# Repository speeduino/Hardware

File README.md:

<div align="center">

[]

##### A low cost, DIY friendly Engine Management System (ECU) based on the Arduino framework
</div>

## Speeduino
The Speeduino project is a flexible, fully featured Engine Management Systems (EMS aka ECU) based on the low cost and open source Arduino platform. It provides the hardware, firmware and software components that make up an engine management system, all provided under open licenses. With over 1000 installations, Speeduino has matured into a product that meets the needs of the hobbyist and enthusiast community without driving prices to the levels of traditional aftermarket ECUs.

## Overview
This repositiory contains the official Speeduino hardware designs. All new designs have been made in Kicad, with some early boards developed in Fritzing. 

## License
These designs are release under the [CERN Open Hardware License v2 Strong (CERN-OHL-S)](https://ohwr.org/cern_ohl_s_v2.txt). 
This license is similar to the GPL, however is designed specifically for hardware design files, including PCB layouts and schematics. As the 'strongly reciprocal' version of the CERN OHL is used, you may use, copy, modify and create variations of these designs freely, provided that any changes or variations are also released under this CERN-OHL-S. 

## Where to Buy
[Pre-made Speeduino units/boards are available from a number of official resellers](https://speeduino.com/home/where-to-buy)

These resellers all contribute a portion of sales back to the project to allow for continued development to take place and we encourage sales through them whenever possible. 
 
Of course, being open source, you are free to use the design files provided here to create your own hardware! 

## Support
In addition the manual referenced above, Speeduino has a large and very vibrant community of people to help out with your setup or any questions you might add. 

* [Speeduino Forum](https://speeduino.com/forum) 
* [Discord](hhttps://discord.com/invite/taXeNM6xNb)
* [Facebook](https://www.facebook.com/groups/191918764521976/)

## Contributors

This project exists thanks to all the people who contribute, both in terms of code and testing provided. If you'd like to get involved, please have a read through [Contributing](contributing.md) and then jump on Discord to discuss things further

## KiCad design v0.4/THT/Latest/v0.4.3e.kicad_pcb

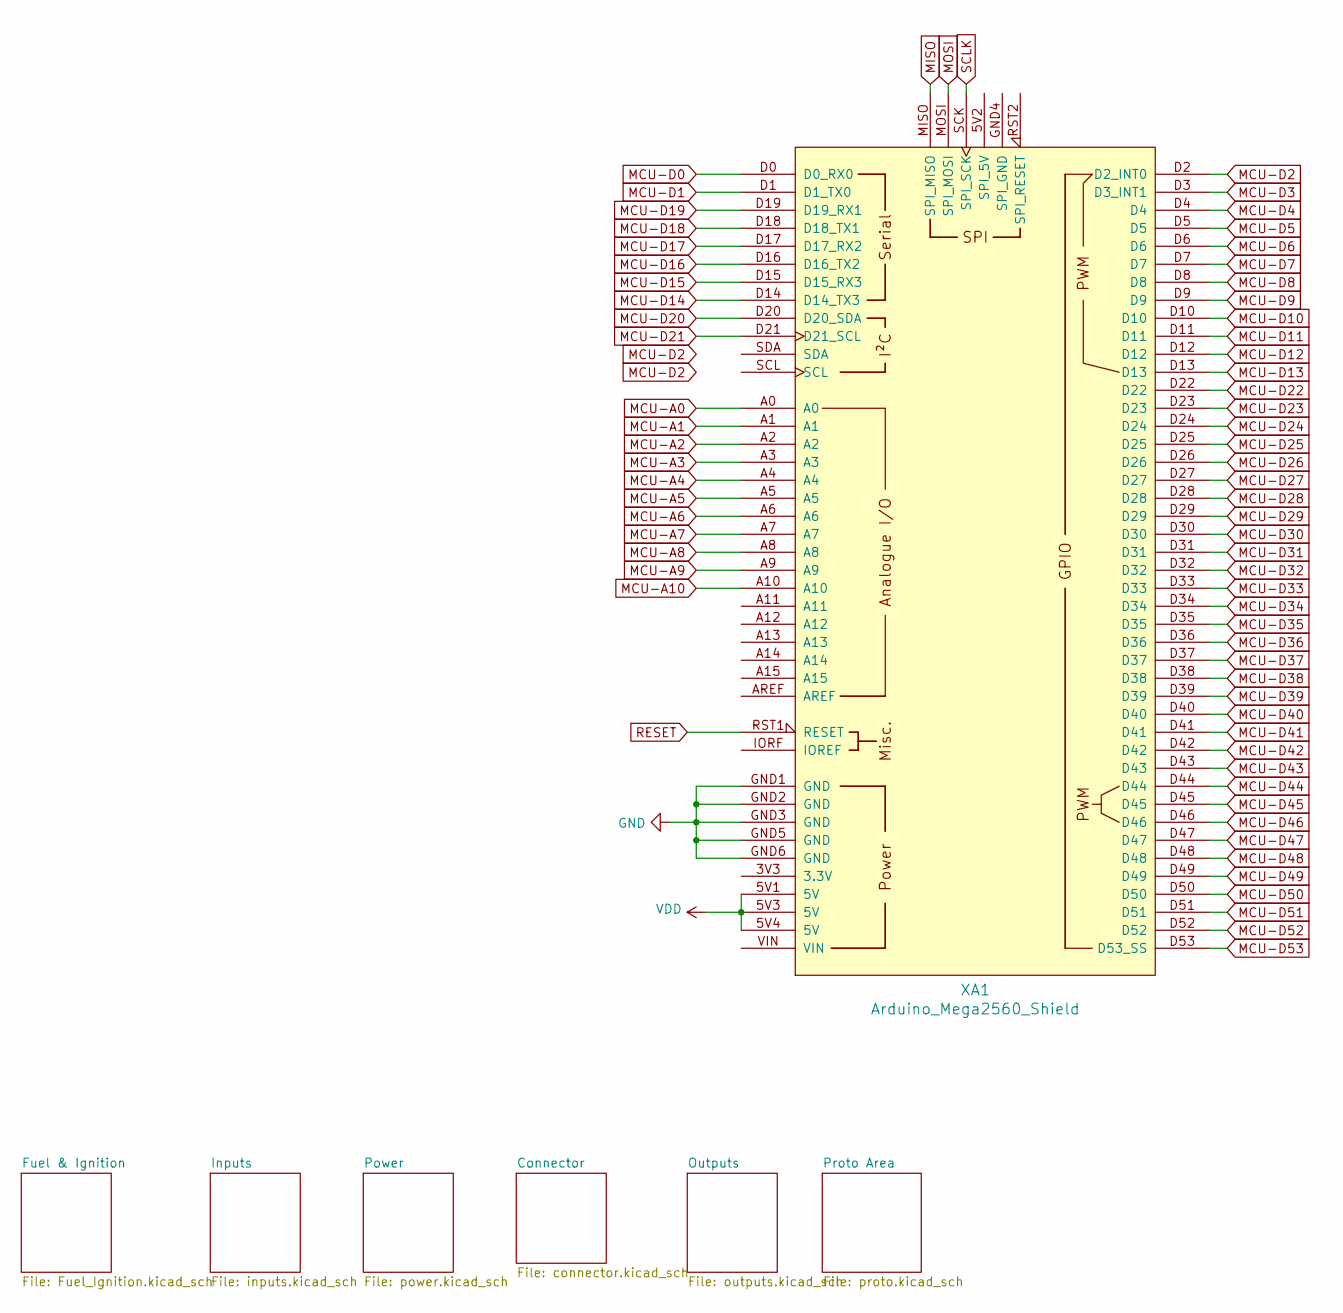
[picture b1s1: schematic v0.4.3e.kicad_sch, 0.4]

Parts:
XA1: Arduino_Mega2560_Shield; Arduino_Mega2560_Shield_IO_Only

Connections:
ADC-Clamp-2: XA1.A3; also elsewhere on the board
ADC-Clamp-3: XA1.A2; also elsewhere on the board
ADC-Clamp-5: XA1.A0; also elsewhere on the board
ADC-Clamp-6: XA1.A1; also elsewhere on the board
ADC-Clamp-7: XA1.D2 (D2_INT0); also elsewhere on the board
ADC-Clamp-8: XA1.D18 (D18_TX1); also elsewhere on the board
ADC-Clamp-9: XA1.D19 (D19_RX1); also elsewhere on the board
ADC-Clamp-10: XA1.D51; also elsewhere on the board
ADC-Clamp-11: XA1.A8; also elsewhere on the board
ADC-Clamp-12: XA1.A4; also elsewhere on the board
GND: XA1.GND1 (GND), XA1.GND2 (GND), XA1.GND3 (GND), XA1.GND5 (GND), XA1.GND6 (GND); also elsewhere on the board
MCU-A5: XA1.A5; also elsewhere on the board
MCU-A6: XA1.A6
MCU-A7: XA1.A7
MCU-A9: XA1.A9; also elsewhere on the board
MCU-A10: XA1.A10; also elsewhere on the board
MCU-D0: XA1.D0 (D0_RX0); also elsewhere on the board
MCU-D1: XA1.D1 (D1_TX0); also elsewhere on the board
MCU-D3: XA1.D3 (D3_INT1); also elsewhere on the board
MCU-D4: XA1.D4; also elsewhere on the board
MCU-D5: XA1.D5; also elsewhere on the board
MCU-D6: XA1.D6; also elsewhere on the board
MCU-D7: XA1.D7; also elsewhere on the board
MCU-D8: XA1.D8; also elsewhere on the board
MCU-D9: XA1.D9; also elsewhere on the board
MCU-D10: XA1.D10; also elsewhere on the board
MCU-D11: XA1.D11; also elsewhere on the board
MCU-D12: XA1.D12
MCU-D13: XA1.D13
MCU-D14: XA1.D14 (D14_TX3)
MCU-D15: XA1.D15 (D15_RX3)
MCU-D16: XA1.D16 (D16_TX2); also elsewhere on the board
MCU-D17: XA1.D17 (D17_RX2); also elsewhere on the board
MCU-D20: XA1.D20 (D20_SDA); also elsewhere on the board
MCU-D21: XA1.D21 (D21_SCL); also elsewhere on the board
MCU-D22: XA1.D22
MCU-D23: XA1.D23
MCU-D24: XA1.D24; also elsewhere on the board
MCU-D25: XA1.D25
MCU-D26: XA1.D26
MCU-D27: XA1.D27
MCU-D28: XA1.D28
MCU-D29: XA1.D29
MCU-D30: XA1.D30
MCU-D31: XA1.D31
MCU-D32: XA1.D32
MCU-D33: XA1.D33
MCU-D34: XA1.D34
MCU-D35: XA1.D35
MCU-D36: XA1.D36
MCU-D37: XA1.D37
MCU-D38: XA1.D38; also elsewhere on the board
MCU-D39: XA1.D39
MCU-D40: XA1.D40; also elsewhere on the board
MCU-D41: XA1.D41
MCU-D42: XA1.D42
MCU-D43: XA1.D43
MCU-D44: XA1.D44
MCU-D45: XA1.D45; also elsewhere on the board
MCU-D46: XA1.D46
MCU-D47: XA1.D47; also elsewhere on the board
MCU-D48: XA1.D48
MCU-D49: XA1.D49; also elsewhere on the board
MCU-D50: XA1.D50; also elsewhere on the board
MCU-D52: XA1.D52; also elsewhere on the board
MCU-D53: XA1.D53 (D53_SS)
RESET: XA1.RST1 (RESET); also elsewhere on the board
VDD: XA1.5V1 (5V), XA1.5V3 (5V), XA1.5V4 (5V); also elsewhere on the board

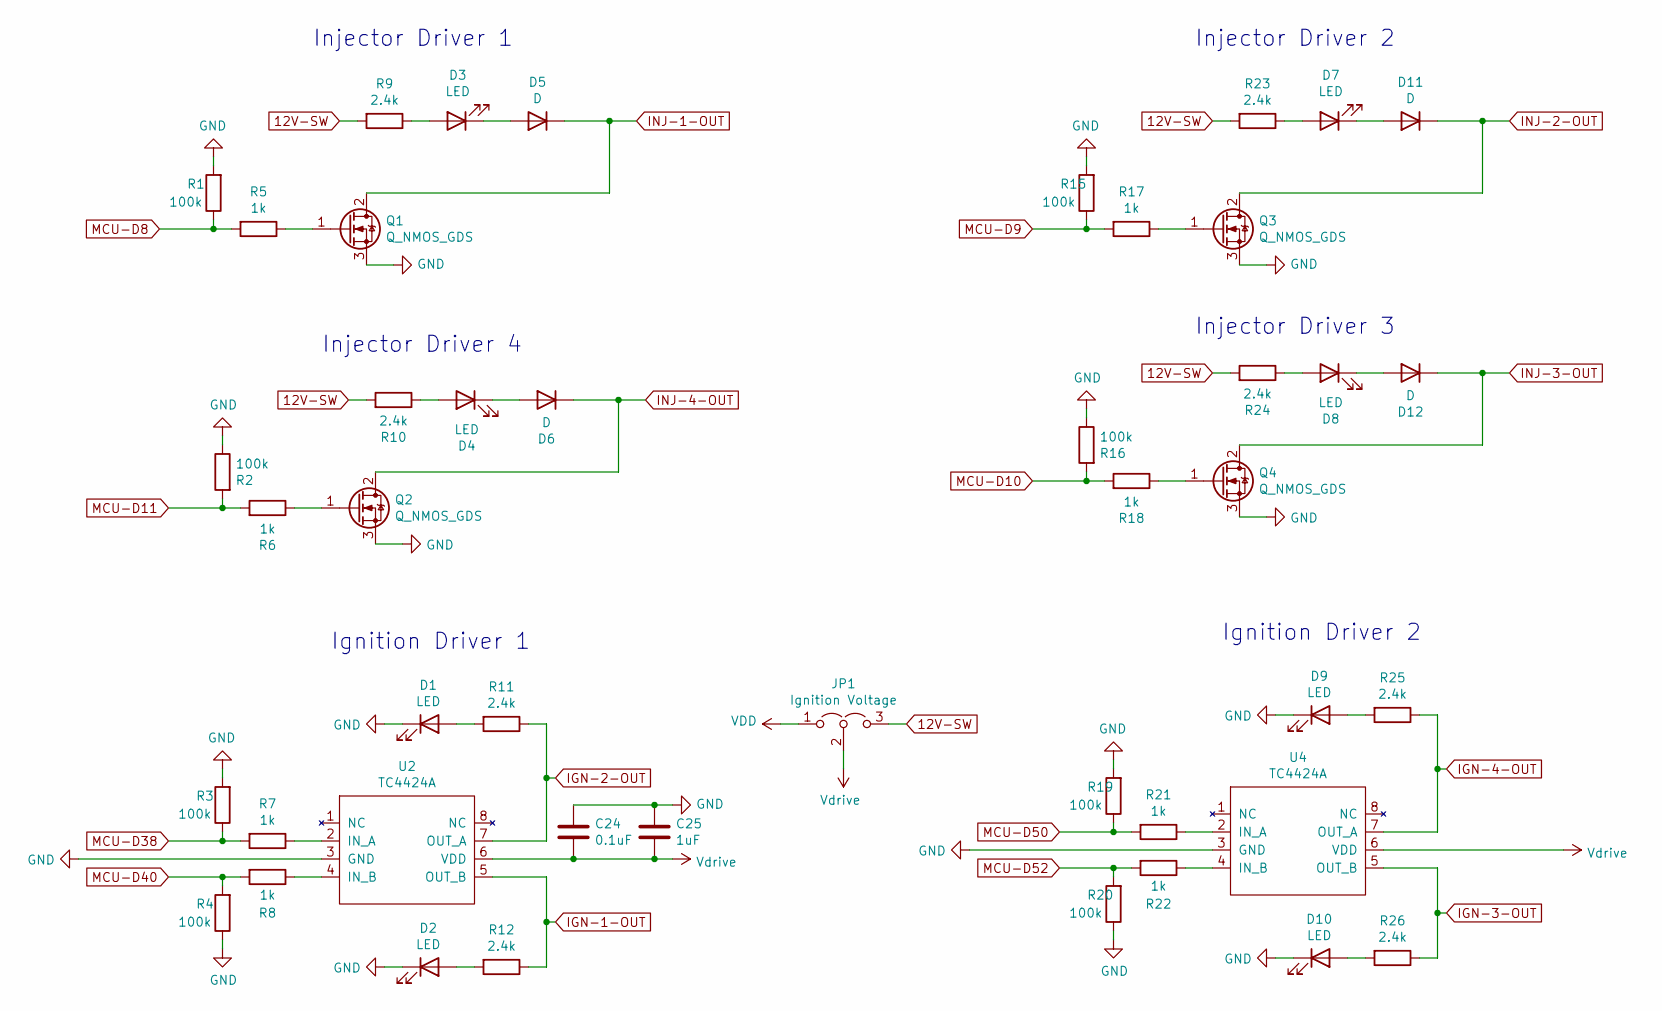
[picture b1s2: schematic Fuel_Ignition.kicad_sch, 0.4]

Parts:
C24: 0.1uF; C_Disc_D5.0mm_W2.5mm_P2.50mm; Manufacturer_Part_Number FA18X8R1E104KNU06; Digikey Part Number 445-180563-1-ND
C25: 1uF; C_Disc_D5.0mm_W2.5mm_P2.50mm; Manufacturer_Part_Number FA18X7R1E105KRU06; Digikey Part Number 445-180543-1-ND
D1, D2, D3, D4, D7, D8, D9, D10: LED; LED_D3.0mm; Manufacturer_Part_Number 151031SS04000; Digikey Part Number 732-5005-ND
D5, D6, D11, D12: D; D_DO-35_SOD27_P7.62mm_Horizontal; Manufacturer_Part_Number 1N914TAP; Digikey Part Number 1N914TAPGICT-ND
JP1: Ignition Voltage; PinHeader_1x03_P2.54mm_Vertical; Manufacturer_Part_Number M20-9990345; Digikey Part Number 952-2263-ND
Q1, Q2, Q3, Q4: Q_NMOS_GDS; TO-220-3_Horizontal_TabDown; Manufacturer_Part_Number STP62NS04Z; Digikey Part Number 497-5896-5-ND
R1, R2, R3, R4, R15, R16, R19, R20: 100k; R_Axial_DIN0204_L3.6mm_D1.6mm_P5.08mm_Horizontal; Manufacturer_Part_Number MBA02040C1003FCT00; Digikey Part Number BC3240CT-ND
R5, R6, R7, R8, R17, R18, R21, R22: 1k; R_Axial_DIN0204_L3.6mm_D1.6mm_P5.08mm_Horizontal; Manufacturer_Part_Number MBA02040C1001FRP00; Digikey Part Number BC1.00KXCT-ND
R9, R10, R11, R12, R23, R24, R25, R26: 2.4k; R_Axial_DIN0204_L3.6mm_D1.6mm_P5.08mm_Horizontal; Manufacturer_Part_Number MBA02040C2401FC100; Digikey Part Number BC3483CT-ND
U2, U4: TC4424A; DIP-8_W7.62mm_Socket; Manufacturer_Part_Number TC4424AVPA; Digikey Part Number TC4424AVPA-ND

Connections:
12V-SW: JP1.3 (B), R9.2, R10.2, R23.2, R24.2; also elsewhere on the board
GND: C24.1, C25.1, D1.1 (K), D2.1 (K), D9.1 (K), D10.1 (K), Q1.3 (S), Q2.3 (S), Q3.3 (S), Q4.3 (S), R1.2, R2.1, R3.2, R4.1, R15.2, R16.1, R19.2, R20.1, U2.3 (GND), U4.3 (GND); also elsewhere on the board
IGN-1-OUT: R12.1, U2.5 (OUT_B); also elsewhere on the board
IGN-2-OUT: R11.1, U2.7 (OUT_A); also elsewhere on the board
IGN-3-OUT: R26.1, U4.5 (OUT_B); also elsewhere on the board
IGN-4-OUT: R25.1, U4.7 (OUT_A); also elsewhere on the board
INJ-1-OUT: D5.1 (K), Q1.2 (D); also elsewhere on the board
INJ-2-OUT: D11.1 (K), Q3.2 (D); also elsewhere on the board
INJ-3-OUT: D12.1 (K), Q4.2 (D); also elsewhere on the board
INJ-4-OUT: D6.1 (K), Q2.2 (D); also elsewhere on the board
MCU-D8: R1.1, R5.2; also elsewhere on the board
MCU-D9: R15.1, R17.2; also elsewhere on the board
MCU-D10: R16.2, R18.2; also elsewhere on the board
MCU-D11: R2.2, R6.2; also elsewhere on the board
MCU-D38: R3.1, R7.2; also elsewhere on the board
MCU-D40: R4.2, R8.2; also elsewhere on the board
MCU-D50: R19.1, R21.2; also elsewhere on the board
MCU-D52: R20.2, R22.2; also elsewhere on the board
unnamed: D1.2 (A), R11.2
unnamed: D2.2 (A), R12.2
unnamed: D3.1 (K), D5.2 (A)
unnamed: D3.2 (A), R9.1
unnamed: D4.1 (K), D6.2 (A)
unnamed: D4.2 (A), R10.1
unnamed: D7.2 (A), R23.1
unnamed: D8.2 (A), R24.1
unnamed: D9.2 (A), R25.2
unnamed: D10.2 (A), R26.2
unnamed: D7.1 (K), D11.2 (A)
unnamed: D8.1 (K), D12.2 (A)
unnamed: Q1.1 (G), R5.1
unnamed: Q2.1 (G), R6.1
unnamed: Q3.1 (G), R17.1
unnamed: Q4.1 (G), R18.1
unnamed: R7.1, U2.2 (IN_A)
unnamed: R8.1, U2.4 (IN_B)
unnamed: R21.1, U4.2 (IN_A)
unnamed: R22.1, U4.4 (IN_B)
VDD: JP1.1 (A); also elsewhere on the board
Vdrive: C24.2, C25.2, JP1.2 (C), U2.6 (VDD), U4.6 (VDD)

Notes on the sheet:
Injector Driver 4
Ignition Driver 1
Injector Driver 3
Injector Driver 2
Injector Driver 1
Ignition Driver 2

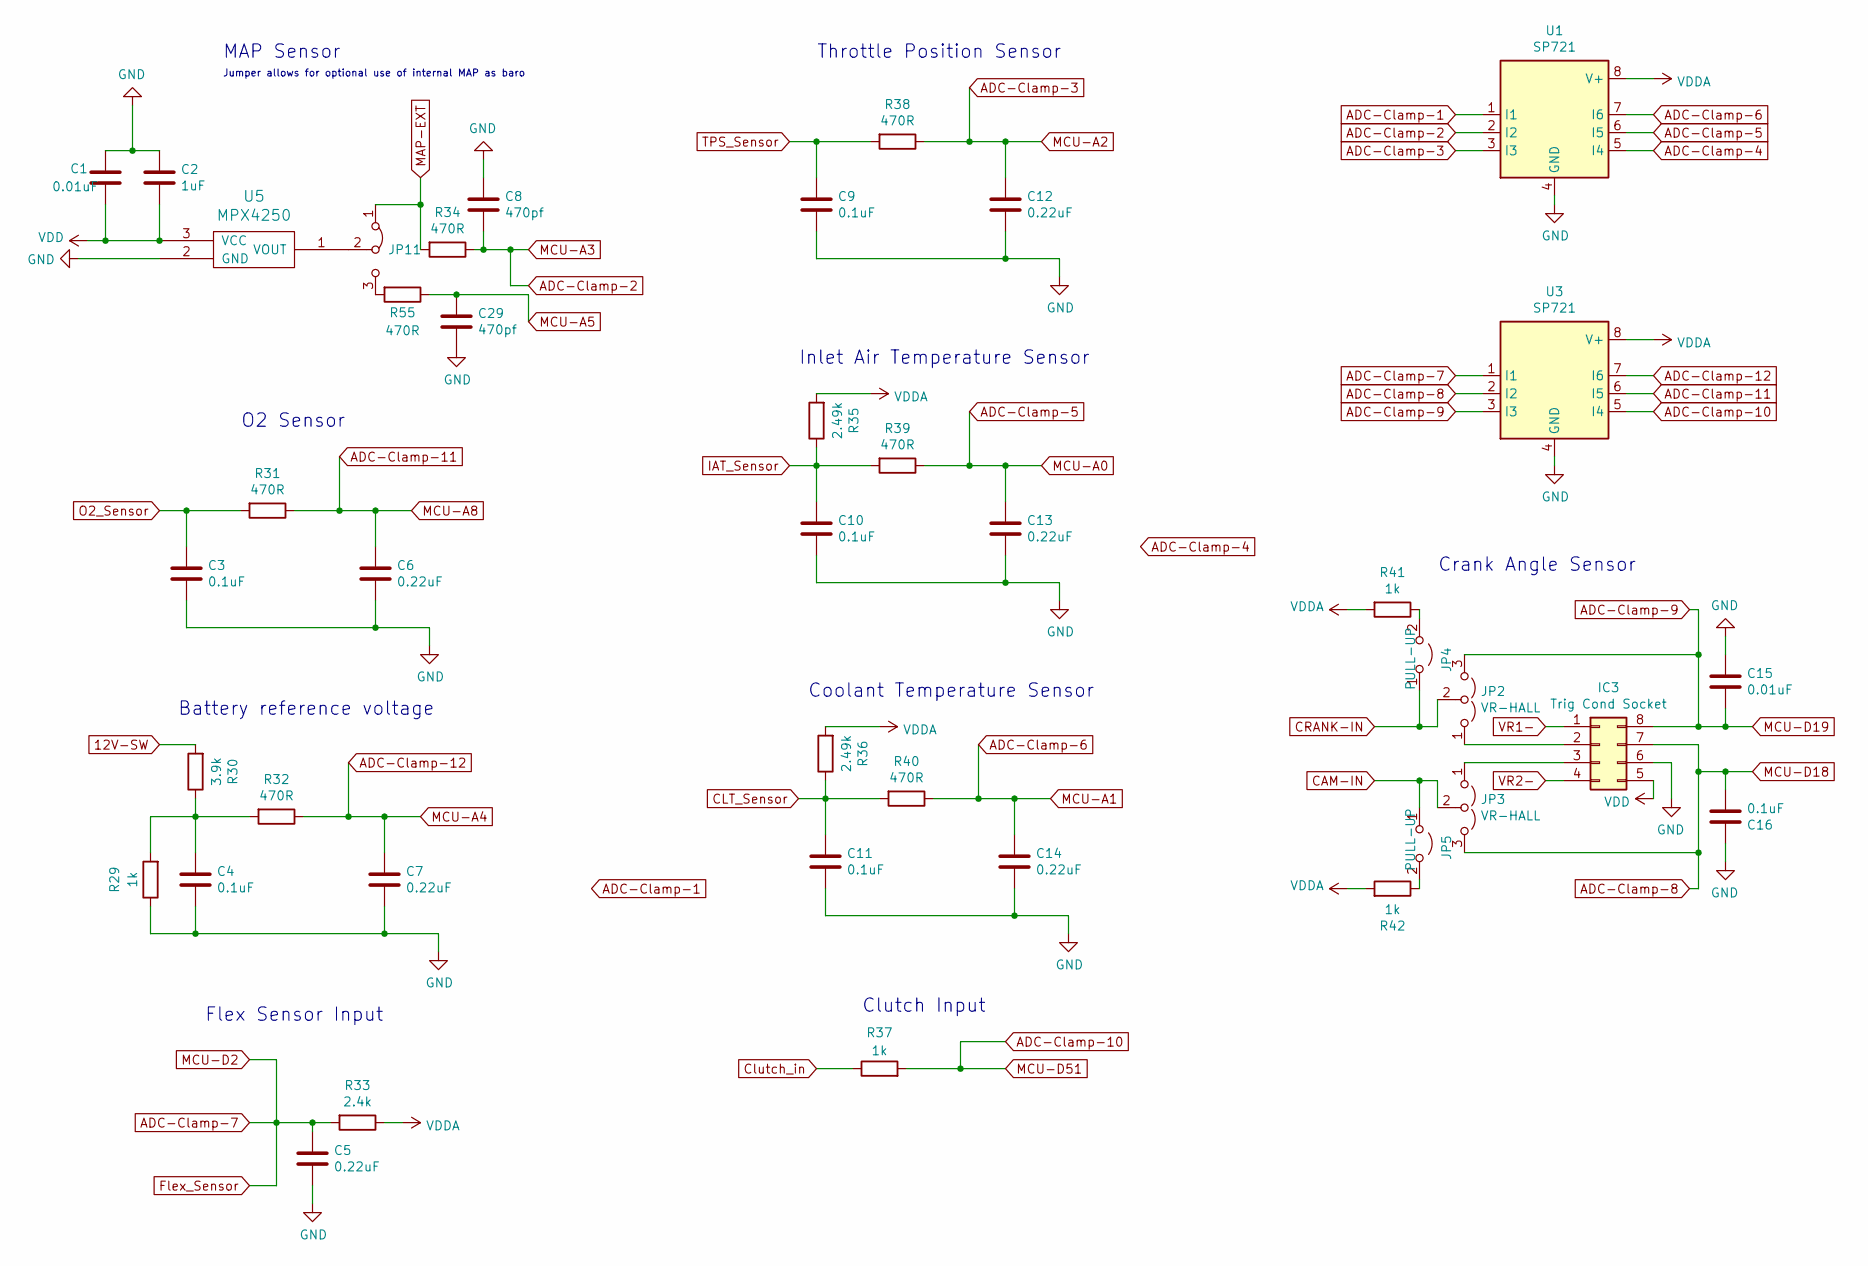
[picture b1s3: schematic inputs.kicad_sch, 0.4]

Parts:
C1, C15: 0.01uF; C_Disc_D5.0mm_W2.5mm_P2.50mm; Manufacturer_Part_Number FA18X7R1H103KNU06; Digikey Part Number 445-174244-1-ND
C2: 1uF; C_Disc_D5.0mm_W2.5mm_P2.50mm; Manufacturer_Part_Number FA18X7R1E105KRU06; Digikey Part Number 445-180543-1-ND
C3, C4, C9, C10, C11, C16: 0.1uF; C_Disc_D5.0mm_W2.5mm_P2.50mm; Manufacturer_Part_Number FA18X8R1E104KNU06; Digikey Part Number 445-180563-1-ND
C5, C6, C7, C12, C13, C14: 0.22uF; C_Disc_D5.0mm_W2.5mm_P2.50mm; Manufacturer_Part_Number FA18X8R1E224KRU06; Digikey Part Number 445-180564-1-ND
C8, C29: 470pf; C_Disc_D5.0mm_W2.5mm_P2.50mm; Manufacturer_Part_Number FA18NP01H471JNU06; Digikey Part Number 445-180522-1-ND
IC3: Trig Cond Socket; DIP-8_W7.62mm_Socket
JP2, JP3: VR-HALL; PinHeader_1x03_P2.54mm_Vertical; Manufacturer_Part_Number M20-9990345; Digikey Part Number 952-2263-ND
JP4, JP5: PULL-UP; PinHeader_1x02_P2.54mm_Vertical; Manufacturer_Part_Number M20-9990245; Digikey Part Number 952-2261-ND
JP11: Jumper_3_Bridged12; SolderJumper-3_P1.3mm_Bridged12_RoundedPad1.0x1.5mm
R29, R37, R41, R42: 1k; R_Axial_DIN0204_L3.6mm_D1.6mm_P5.08mm_Horizontal; Manufacturer_Part_Number MBA02040C1001FRP00; Digikey Part Number BC1.00KXCT-ND
R30: 3.9k; R_Axial_DIN0204_L3.6mm_D1.6mm_P5.08mm_Horizontal; Manufacturer_Part_Number MBA02040C3901FCT00; Digikey Part Number BC3272CT-ND
R31, R32, R34, R38, R39, R40, R55: 470R; R_Axial_DIN0204_L3.6mm_D1.6mm_P5.08mm_Horizontal; Manufacturer_Part_Number MBA02040C4700FRP00; Digikey Part Number BC3516CT-ND
R33: 2.4k; R_Axial_DIN0204_L3.6mm_D1.6mm_P5.08mm_Horizontal; Manufacturer_Part_Number MBA02040C2401FC100; Digikey Part Number BC3483CT-ND
R35, R36: 2.49k; R_Axial_DIN0204_L3.6mm_D1.6mm_P5.08mm_Horizontal; Manufacturer_Part_Number MBA02040C2491FRP00; Digikey Part Number BC2.49KXCT-ND
U1, U3: SP721; DIP-8_W7.62mm; Manufacturer_Part_Number SP721APP; Digikey Part Number F2720-ND
U5: MPX4250; Manufacturer_Part_Number MPX4250AP; Digikey Part Number MPX4250AP-ND

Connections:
12V-SW: R30.2; also elsewhere on the board
ADC-Clamp-1: U1.1 (I1)
ADC-Clamp-2: C8.2, R34.1, U1.2 (I2); also elsewhere on the board
ADC-Clamp-3: C12.1, R38.1, U1.3 (I3); also elsewhere on the board
ADC-Clamp-4: U1.5 (I4)
ADC-Clamp-5: C13.1, R39.1, U1.6 (I5); also elsewhere on the board
ADC-Clamp-6: C14.1, R40.1, U1.7 (I6); also elsewhere on the board
ADC-Clamp-7: C5.1, R33.2, U3.1 (I1); also elsewhere on the board
ADC-Clamp-8: C16.2, IC3.7, JP3.3 (B), U3.2 (I2); also elsewhere on the board
ADC-Clamp-9: C15.2, IC3.8, JP2.3 (B), U3.3 (I3); also elsewhere on the board
ADC-Clamp-10: R37.2, U3.5 (I4); also elsewhere on the board
ADC-Clamp-11: C6.1, R31.1, U3.6 (I5); also elsewhere on the board
ADC-Clamp-12: C7.1, R32.1, U3.7 (I6); also elsewhere on the board
CAM-IN: JP3.2 (C), JP5.1 (A); also elsewhere on the board
CLT_Sensor: C11.1, R36.1, R40.2; also elsewhere on the board
CRANK-IN: JP2.2 (C), JP4.1 (A); also elsewhere on the board
Clutch_in: R37.1; also elsewhere on the board
GND: C1.1, C2.1, C3.2, C4.2, C5.2, C6.2, C7.2, C8.1, C9.2, C10.2, C11.2, C12.2, C13.2, C14.2, C15.1, C16.1, C29.2, IC3.6, R29.1, U1.4 (GND), U3.4 (GND), U5.2 (GND); also elsewhere on the board
IAT_Sensor: C10.1, R35.1, R39.2; also elsewhere on the board
MAP-EXT: JP11.1 (A), R34.2; also elsewhere on the board
MCU-A5: C29.1, R55.1; also elsewhere on the board
unnamed: C4.1, R29.2, R30.1, R32.2
unnamed: IC3.2, JP2.1 (A)
unnamed: IC3.3, JP3.1 (A)
unnamed: JP4.2 (B), R41.1
unnamed: JP5.2 (B), R42.1
unnamed: JP11.2 (C), U5.1 (VOUT)
unnamed: JP11.3 (B), R55.2
O2_Sensor: C3.1, R31.2; also elsewhere on the board
TPS_Sensor: C9.1, R38.2; also elsewhere on the board
VDD: C1.2, C2.2, IC3.5, U5.3 (VCC); also elsewhere on the board
VDDA: R33.1, R35.2, R36.2, R41.2, R42.2, U1.8 (V+), U3.8 (V+); also elsewhere on the board
VR1-: IC3.1; also elsewhere on the board
VR2-: IC3.4; also elsewhere on the board

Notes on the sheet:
MAP Sensor
Crank Angle Sensor
Battery reference voltage
Coolant Temperature Sensor
Clutch Input
Throttle Position Sensor
Inlet Air Temperature Sensor
O2 Sensor
Jumper allows for optional use of internal MAP as baro
Flex Sensor Input

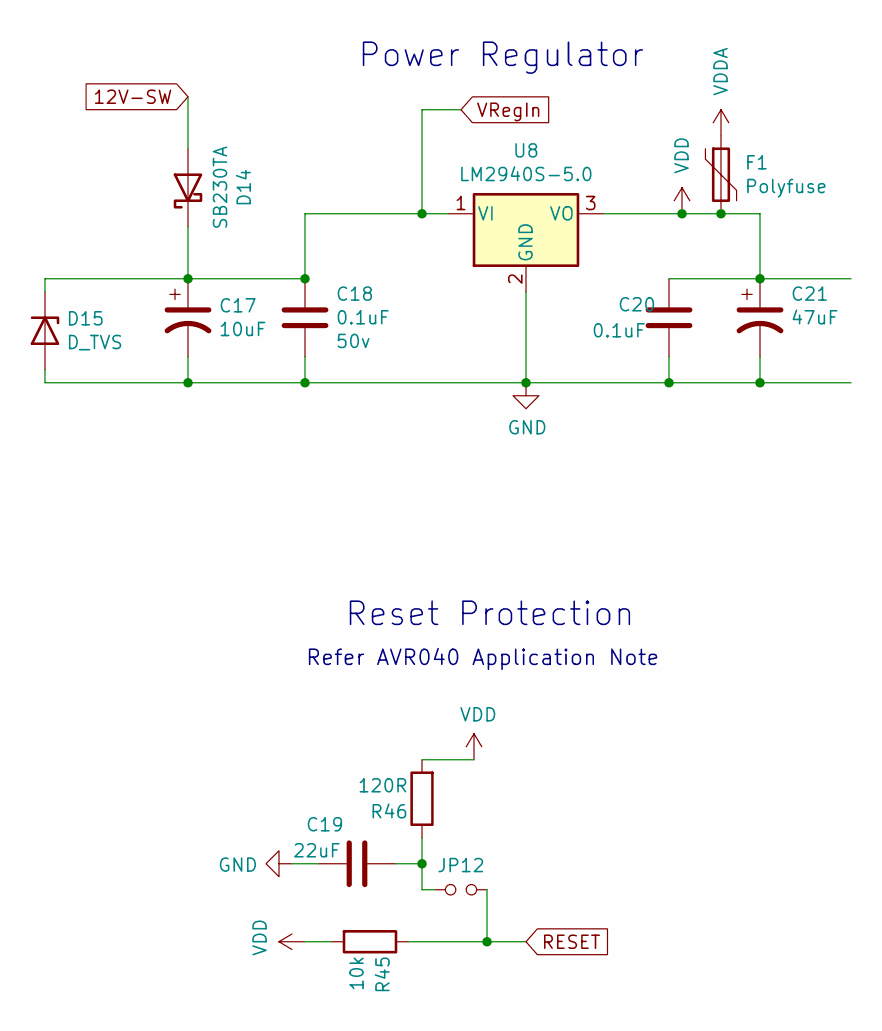
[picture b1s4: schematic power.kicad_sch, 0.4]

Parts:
C17: 10uF; CP_Radial_D5.0mm_P2.00mm; Voltage 50v; Manufacturer_Part_Number EEU-FC1H100L; Digikey Part Number P10316-ND
C18: 0.1uF; C_Disc_D5.0mm_W2.5mm_P2.50mm; Voltage 50v; Manufacturer_Part_Number FA18X8R1E104KNU06; Digikey Part Number 445-180563-1-ND
C19: 22uF; C_Disc_D7.5mm_W5.0mm_P5.00mm; Manufacturer_Part_Number FA22X7R1E226MRU06; Digikey Part Number 445-180603-1-ND
C20: 0.1uF; C_Disc_D5.0mm_W2.5mm_P2.50mm; Manufacturer_Part_Number FA18X8R1E104KNU06; Digikey Part Number 445-180563-1-ND
C21: 47uF; CP_Radial_D8.0mm_P5.00mm; Manufacturer_Part_Number EEU-FC1H470B; Digikey Part Number P19658CT-ND
D14: SB230TA; D_DO-41_SOD81_P7.62mm_Horizontal; Manufacturer_Part_Number SB230TA; Digikey Part Number 1655-1518-1-ND
D15: D_TVS; D_DO-15_P12.70mm_Horizontal; Manufacturer_Part_Number TP6KE47A; Digikey Part Number F6853CT-ND
F1: Polyfuse; Fuse_BelFuse_0ZRE0055FF_L14.0mm_W4.1mm; Manufacturer_Part_Number 0ZRP0050FF1E; Digikey Part Number 507-2403-ND
JP12: Jumper_NO_Small; PinHeader_1x02_P2.54mm_Vertical
R45: 10k; R_Axial_DIN0204_L3.6mm_D1.6mm_P5.08mm_Horizontal; Manufacturer_Part_Number MBA02040C1002FRP00; Digikey Part Number BC10.0KXCT-ND
R46: 120R; R_Axial_DIN0204_L3.6mm_D1.6mm_P5.08mm_Horizontal; Manufacturer_Part_Number MBA02040C1200FC100; Digikey Part Number BC3453CT-ND
U8: LM2940S-5.0; TO-220-3_Horizontal_TabDown; Manufacturer_Part_Number NCV7805BTG; Digikey Part Number NCV7805BTGOS-ND

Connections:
12V-SW: D14.2 (A); also elsewhere on the board
GND: C17.2, C18.2, C19.2, C20.2, C21.2, D15.2 (A), U8.2 (GND); also elsewhere on the board
unnamed: C19.1, JP12.1, R46.1
RESET: JP12.2, R45.1; also elsewhere on the board
VDD: C20.1, C21.1, F1.2, R45.2, R46.2, U8.3 (VO); also elsewhere on the board
VDDA: F1.1; also elsewhere on the board
VRegIn: C17.1, C18.1, D14.1 (K), D15.1 (K), U8.1 (VI)

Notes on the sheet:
Power Regulator
Refer AVR040 Application Note
Reset Protection

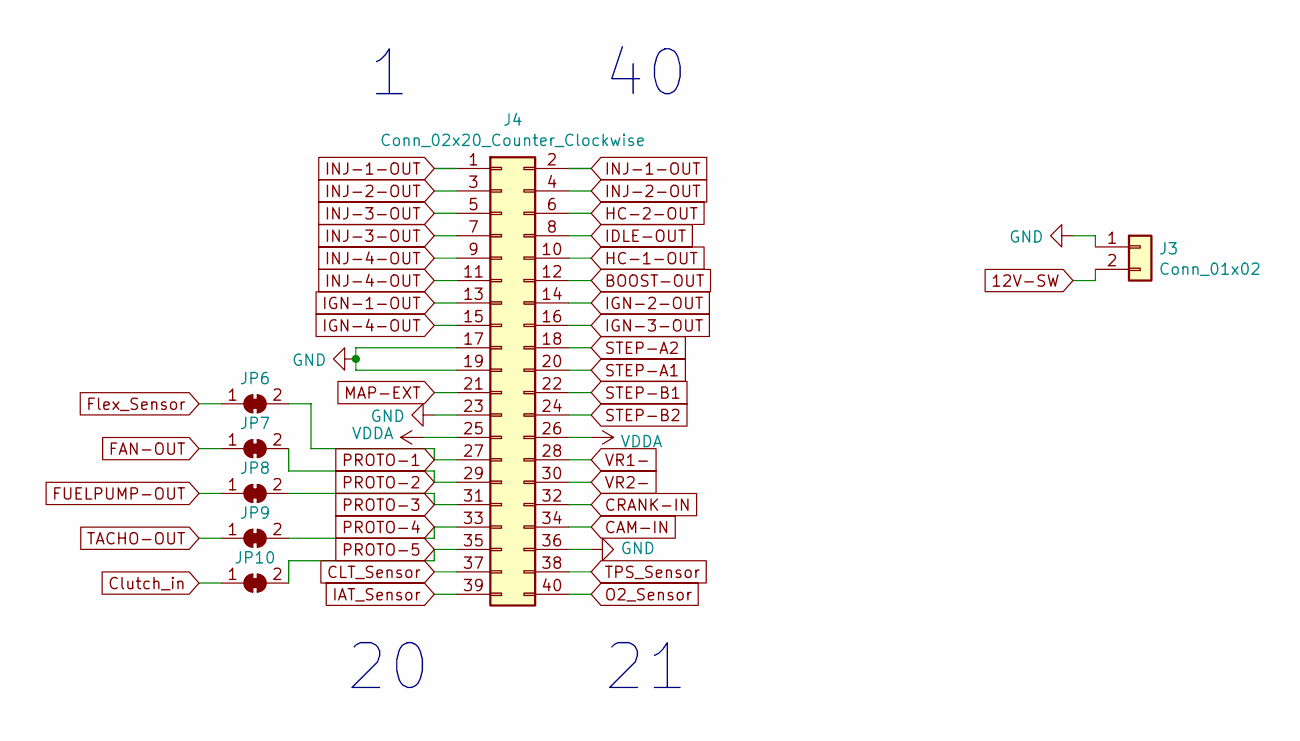
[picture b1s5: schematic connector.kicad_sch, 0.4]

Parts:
J3: Conn_01x02; TerminalBlock_Phoenix_PT-1,5-2-5.0-H_1x02_P5.00mm_Horizontal
J4: Conn_02x20_Counter_Clockwise; IDC-Header_2x20_P2.54mm_Vertical
JP6, JP7, JP8, JP9, JP10: SolderJumper_2_Bridged; SolderJumper-2_P1.3mm_Bridged_Pad1.0x1.5mm

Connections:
12V-SW: J3.2; also elsewhere on the board
ADC-Clamp-7: JP6.1 (A); also elsewhere on the board
BOOST-OUT: J4.12; also elsewhere on the board
CAM-IN: J4.34; also elsewhere on the board
CLT_Sensor: J4.37; also elsewhere on the board
CRANK-IN: J4.32; also elsewhere on the board
Clutch_in: JP10.1 (A); also elsewhere on the board
FAN-OUT: JP7.1 (A); also elsewhere on the board
FUELPUMP-OUT: JP8.1 (A); also elsewhere on the board
GND: J3.1, J4.17, J4.19, J4.23, J4.36; also elsewhere on the board
HC-1-OUT: J4.10; also elsewhere on the board
IAT_Sensor: J4.39; also elsewhere on the board
IGN-1-OUT: J4.13; also elsewhere on the board
IGN-2-OUT: J4.14; also elsewhere on the board
IGN-3-OUT: J4.16; also elsewhere on the board
IGN-4-OUT: J4.15; also elsewhere on the board
INJ-1-OUT: J4.1, J4.2; also elsewhere on the board
INJ-2-OUT: J4.3, J4.4; also elsewhere on the board
INJ-3-OUT: J4.5, J4.7; also elsewhere on the board
INJ-4-OUT: J4.9, J4.11; also elsewhere on the board
MAP-EXT: J4.21; also elsewhere on the board
O2_Sensor: J4.40; also elsewhere on the board
PROTO-1: J4.27, JP6.2 (B)
PROTO-2: J4.29, JP7.2 (B)
PROTO-3: J4.31, JP8.2 (B)
PROTO-4: J4.33, JP9.2 (B)
PROTO-5: J4.35, JP10.2 (B)
STEP-A1: J4.20; also elsewhere on the board
STEP-A2: J4.18; also elsewhere on the board
STEP-B1: J4.22; also elsewhere on the board
STEP-B2: J4.24; also elsewhere on the board
TACHO-OUT: JP9.1 (A); also elsewhere on the board
TPS_Sensor: J4.38; also elsewhere on the board
VDDA: J4.25, J4.26; also elsewhere on the board
VR1-: J4.28; also elsewhere on the board
VR2-: J4.30; also elsewhere on the board

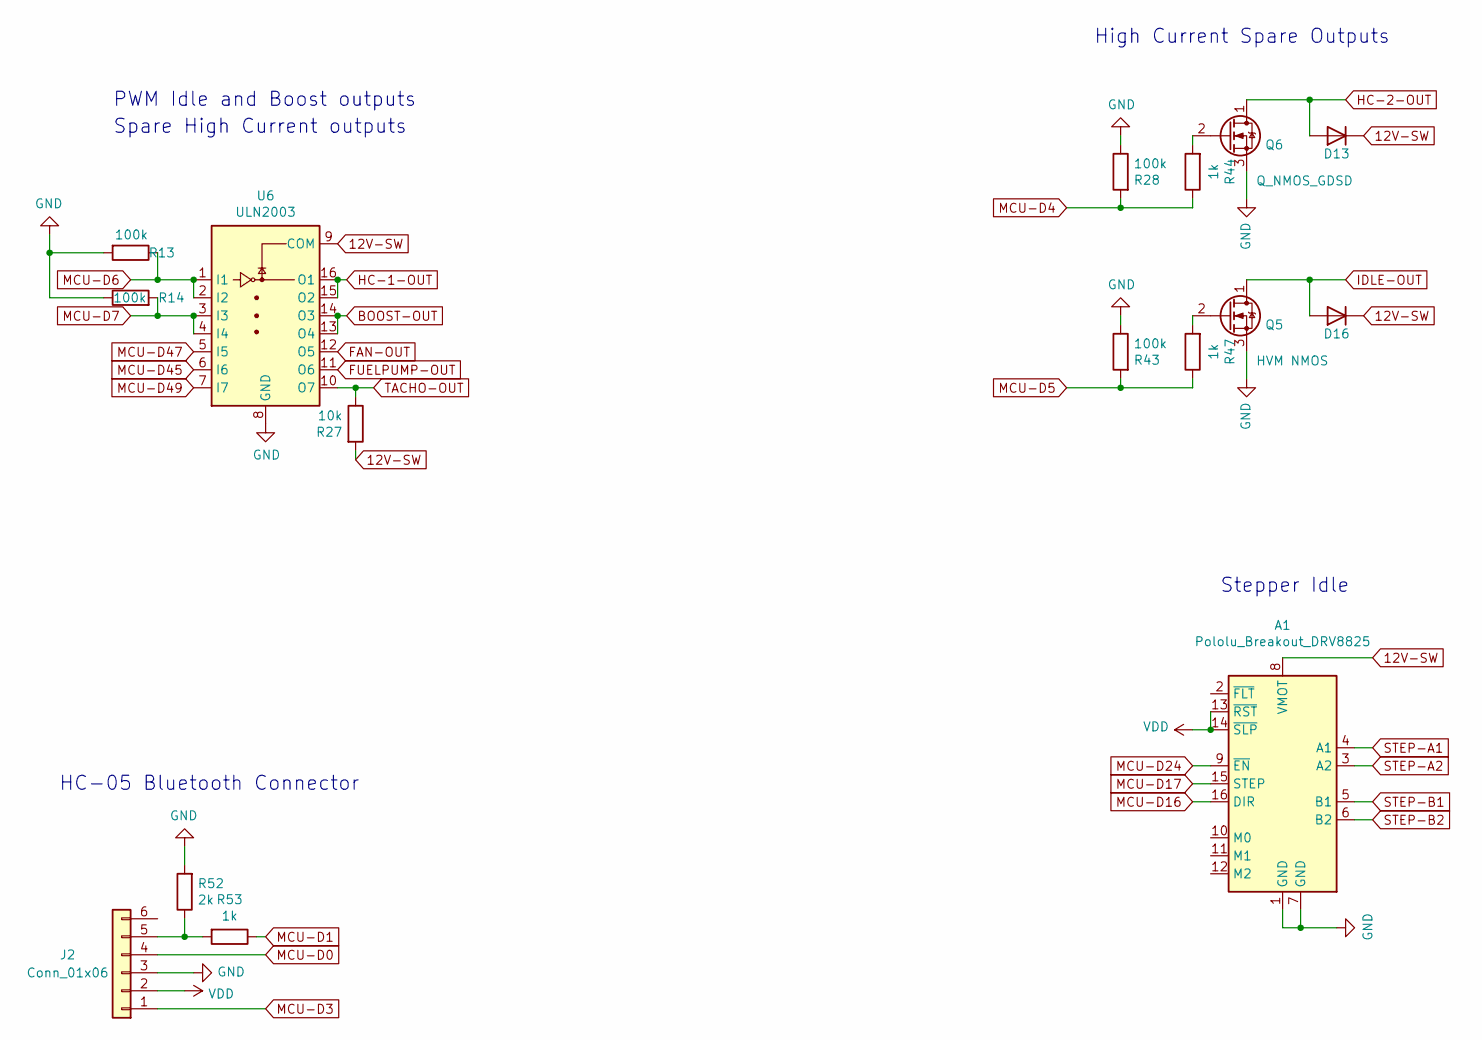
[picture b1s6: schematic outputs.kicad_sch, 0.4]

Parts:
A1: Pololu_Breakout_DRV8825; Pololu_Breakout-16_15.2x20.3mm
D13, D16: D; D_DO-35_SOD27_P7.62mm_Horizontal; Manufacturer_Part_Number 1N914TAP; Digikey Part Number 1N914TAPGICT-ND
J2: Conn_01x06; PinHeader_1x06_P2.54mm_Vertical
Q5: HVM NMOS; Vishay_HVM-DIP-3_W7.62mm; Manufacturer_Part_Number IRLD024PBF; Digikey Part Number IRLD024PBF-ND
Q6: Q_NMOS_GDSD; Vishay_HVM-DIP-3_W7.62mm; Manufacturer_Part_Number IRLD024PBF; Digikey Part Number IRLD024PBF-ND
R13, R14, R28, R43: 100k; R_Axial_DIN0204_L3.6mm_D1.6mm_P5.08mm_Horizontal; Manufacturer_Part_Number MBA02040C1003FCT00; Digikey Part Number BC3240CT-ND
R27: 10k; R_Axial_DIN0204_L3.6mm_D1.6mm_P5.08mm_Horizontal; Manufacturer_Part_Number MBA02040C1002FRP00; Digikey Part Number BC10.0KXCT-ND
R44, R47, R53: 1k; R_Axial_DIN0204_L3.6mm_D1.6mm_P5.08mm_Horizontal; Manufacturer_Part_Number MBA02040C1001FRP00; Digikey Part Number BC1.00KXCT-ND
R52: 2k; R_Axial_DIN0204_L3.6mm_D1.6mm_P5.08mm_Horizontal; Manufacturer_Part_Number MBA02040C2001FCT00; Digikey Part Number BC3254CT-ND
U6: ULN2003; DIP-16_W7.62mm; Manufacturer_Part_Number ULN2003AIN‎; Digikey Part Number 296-16971-5-ND

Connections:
12V-SW: A1.8 (VMOT), D13.1 (K), D16.1 (K), R27.2, U6.9 (COM); also elsewhere on the board
BOOST-OUT: U6.13 (O4), U6.14 (O3); also elsewhere on the board
FAN-OUT: U6.12 (O5); also elsewhere on the board
FUELPUMP-OUT: U6.11 (O6); also elsewhere on the board
GND: A1.1 (GND), A1.7 (GND), J2.3, Q5.3 (S), Q6.3 (S), R13.2, R14.1, R28.1, R43.1, R52.2, U6.8 (GND); also elsewhere on the board
HC-1-OUT: U6.15 (O2), U6.16 (O1); also elsewhere on the board
MCU-D0: J2.4; also elsewhere on the board
MCU-D1: R53.1; also elsewhere on the board
MCU-D3: J2.1; also elsewhere on the board
MCU-D4: R28.2, R44.1; also elsewhere on the board
MCU-D5: R43.2, R47.1; also elsewhere on the board
MCU-D6: R13.1, U6.1 (I1), U6.2 (I2); also elsewhere on the board
MCU-D7: R14.2, U6.3 (I3), U6.4 (I4); also elsewhere on the board
MCU-D16: A1.16 (DIR); also elsewhere on the board
MCU-D17: A1.15 (STEP); also elsewhere on the board
MCU-D24: A1.9 (~EN); also elsewhere on the board
MCU-D45: U6.6 (I6); also elsewhere on the board
MCU-D47: U6.5 (I5); also elsewhere on the board
MCU-D49: U6.7 (I7); also elsewhere on the board
unnamed: J2.5, R52.1, R53.2
STEP-A1: A1.4 (A1); also elsewhere on the board
STEP-A2: A1.3 (A2); also elsewhere on the board
STEP-B1: A1.5 (B1); also elsewhere on the board
STEP-B2: A1.6 (B2); also elsewhere on the board
TACHO-OUT: R27.1, U6.10 (O7); also elsewhere on the board
VDD: A1.13 (~RST), A1.14 (~SLP), J2.2; also elsewhere on the board

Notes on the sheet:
Stepper Idle
Spare High Current outputs
PWM Idle and Boost outputs
HC-05 Bluetooth Connector
High Current Spare Outputs

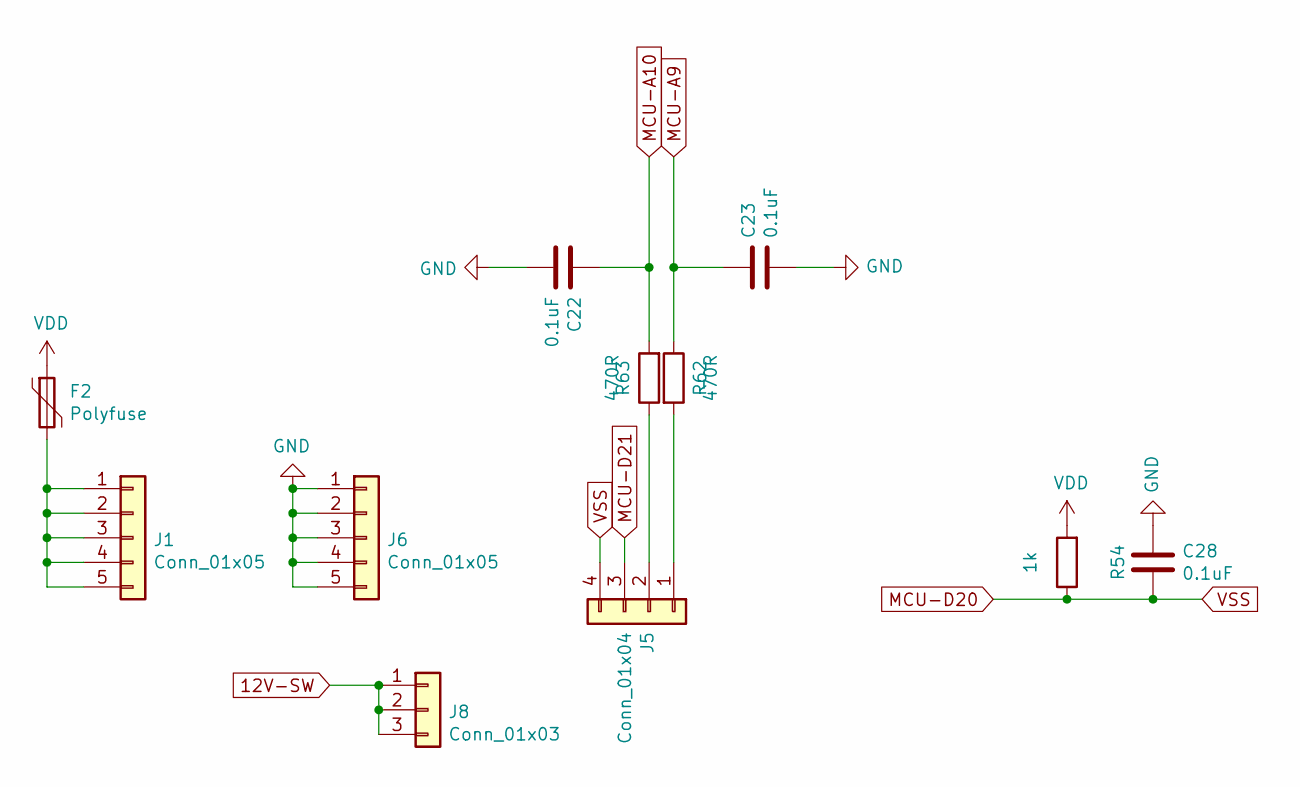
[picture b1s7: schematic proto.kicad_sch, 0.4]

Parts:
C22, C23, C28: 0.1uF; C_Disc_D5.0mm_W2.5mm_P2.50mm; Manufacturer_Part_Number FA18X8R1E104KNU06; Digikey Part Number 445-180563-1-ND
F2: Polyfuse; Fuse_BelFuse_0ZRE0055FF_L14.0mm_W4.1mm; Manufacturer_Part_Number 0ZRP0050FF1E; Digikey Part Number 507-2403-ND
J1, J6: Conn_01x05; PinHeader_1x05_P2.54mm_Vertical
J5: Conn_01x04; PinHeader_1x04_P2.54mm_Vertical
J8: Conn_01x03; PinHeader_1x03_P2.54mm_Vertical
R54: 1k; R_Axial_DIN0204_L3.6mm_D1.6mm_P5.08mm_Horizontal; Manufacturer_Part_Number MBA02040C1001FRP00; Digikey Part Number BC1.00KXCT-ND
R62, R63: 470R; R_Axial_DIN0204_L3.6mm_D1.6mm_P5.08mm_Horizontal; Manufacturer_Part_Number MBA02040C4700FRP00; Digikey Part Number BC3516CT-ND

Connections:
12V-SW: J8.1, J8.2, J8.3; also elsewhere on the board
GND: C22.2, C23.2, C28.1, J6.1, J6.2, J6.3, J6.4, J6.5; also elsewhere on the board
MCU-A9: C23.1, R63.1; also elsewhere on the board
MCU-A10: C22.1, R62.2; also elsewhere on the board
MCU-D20: C28.2, J5.4, R54.1; also elsewhere on the board
MCU-D21: J5.3; also elsewhere on the board
unnamed: F2.2, J1.1, J1.2, J1.3, J1.4, J1.5
unnamed: J5.1, R63.2
unnamed: J5.2, R62.1
VDD: F2.1, R54.2; also elsewhere on the board

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

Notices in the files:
DropBear/MAP Card/v0.3/MAP Card.kicad_pcb:
© Josh Stewart
DropBear/V1.1/DropBear.kicad_pcb:
Drop Bear V1.1 (CERN-OHL-S)
VR Conditioner/Latest/VR-Conditioner-MAX9926+reg.kicad_pcb:
(c)2021 Phill Rogers @ TechColab.co.je
parts and their libraries:
Copyright 2016 Accelerated Designs. All rights reserved.
